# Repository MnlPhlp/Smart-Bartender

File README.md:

# Smart Bartender
This is a modified version of the [smart-bartender](https://youtu.be/2DopvpNF7J4) from Hacker Shack. It can be controlled via a webpage or an alexa skill.

For the building and electronics part watch the video or check the [hackster.io page](https://www.hackster.io/hackershack/smart-bartender-5c430e) of the original project.

## changes in the build
- switched the peristaltic pump for some cheaper and faster water pumps like [these](https://www.ebay.de/itm/131976810073?var=432870985005)
- using a [neopixel ring](https://www.adafruit.com/product/1463) for lighting
- using a [raspberry pi zero](https://www.raspberrypi.org/products/raspberry-pi-zero/) for control

## setup
To setup your pi you need to first install [circuitpython](https://learn.adafruit.com/circuitpython-on-raspberrypi-linux/installing-circuitpython-on-raspberry-pi). After that run:
```
curl https://raw.githubusercontent.com/MnlPhlp/Smart-Bartender/master/setup.sh | bash
```
This will clone the repository, create a venv and install necessary libraries. 
## start
To run the bartender `cd` into Smart-Bartender and start the program with:
```
sudo python bartender.py
```
> sudo is required for the neopixels to work

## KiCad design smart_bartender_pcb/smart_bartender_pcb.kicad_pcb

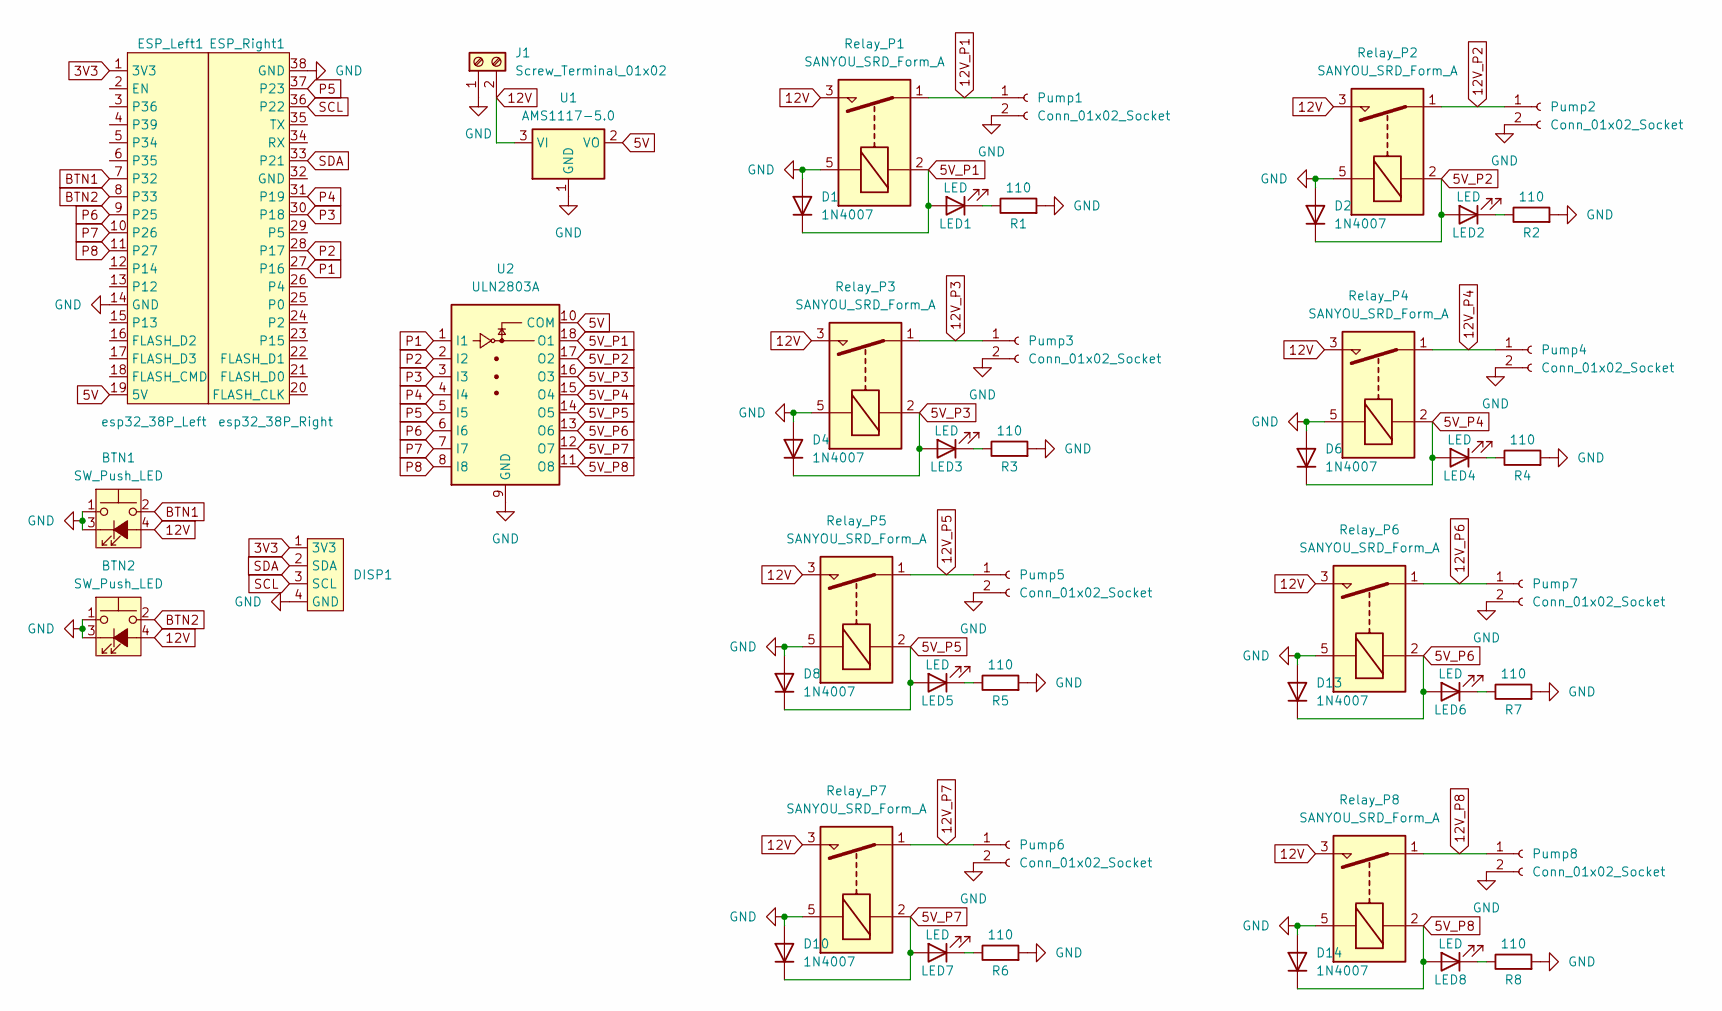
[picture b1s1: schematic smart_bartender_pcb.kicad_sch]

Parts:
BTN1, BTN2: SW_Push_LED; PinHeader_1x04_P2.54mm_Vertical; LCSC C5116483
D1, D2, D4, D6, D8, D10, D13, D14: 1N4007; D_SOD-123; LCSC C3018540
DISP1: PinSocket_1x04_P2.54mm_Horizontal; LCSC C5333413
ESP_Left1: esp32_38P_Left; esp32_38P_left; LCSC C319202
ESP_Right1: esp32_38P_Right; esp32_38P_right; LCSC C319202
J1: Screw_Terminal_01x02; TerminalBlock_Philmore_TB132_1x02_P5.00mm_Horizontal; LCSC C8385
LED1, LED2, LED3, LED4, LED5, LED6, LED7, LED8: LED; LED_0805_2012Metric; LCSC C2297
Pump1, Pump2, Pump3, Pump4, Pump5, Pump6, Pump7, Pump8: Conn_01x02_Socket; SolderWire-1.5sqmm_1x02_P6mm_D1.7mm_OD3mm_Relief
R1, R2, R3, R4, R5, R6, R7, R8: 110; R_0603_1608Metric; LCSC C22781
Relay_P1, Relay_P2, Relay_P3, Relay_P4, Relay_P5, Relay_P6, Relay_P7, Relay_P8: SANYOU_SRD_Form_A; Relay_SPST_SANYOU_SRD_Series_Form_A; LCSC C688862
U1: AMS1117-5.0; SOT-223-3_TabPin2
U2: ULN2803A; SOP-18_7.495x11.515mm_P1.27mm; LCSC C5252904

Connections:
3V3: DISP1.1 (3V3), ESP_Left1.1 (3V3)
5V: ESP_Left1.19 (5V), U1.2 (VO), U2.10 (COM)
5V_P1: D1.1 (K), LED1.2 (A), Relay_P1.2, U2.18 (O1)
5V_P2: D2.1 (K), LED2.2 (A), Relay_P2.2, U2.17 (O2)
5V_P3: D4.1 (K), LED3.2 (A), Relay_P3.2, U2.16 (O3)
5V_P4: D6.1 (K), LED4.2 (A), Relay_P4.2, U2.15 (O4)
5V_P5: D8.1 (K), LED5.2 (A), Relay_P5.2, U2.14 (O5)
5V_P6: D13.1 (K), LED6.2 (A), Relay_P6.2, U2.13 (O6)
5V_P7: D10.1 (K), LED7.2 (A), Relay_P7.2, U2.12 (O7)
5V_P8: D14.1 (K), LED8.2 (A), Relay_P8.2, U2.11 (O8)
12V: BTN1.4 (A), BTN2.4 (A), J1.2, Relay_P1.3, Relay_P2.3, Relay_P3.3, Relay_P4.3, Relay_P5.3, Relay_P6.3, Relay_P7.3, Relay_P8.3, U1.3 (VI)
12V_P1: Pump1.1, Relay_P1.1
12V_P2: Pump2.1, Relay_P2.1
12V_P3: Pump3.1, Relay_P3.1
12V_P4: Pump4.1, Relay_P4.1
12V_P5: Pump5.1, Relay_P5.1
12V_P6: Pump7.1, Relay_P6.1
12V_P7: Pump6.1, Relay_P7.1
12V_P8: Pump8.1, Relay_P8.1
BTN1: BTN1.2, ESP_Left1.7 (P32)
BTN2: BTN2.2, ESP_Left1.8 (P33)
GND: BTN1.1, BTN1.3 (K), BTN2.1, BTN2.3 (K), D1.2 (A), D2.2 (A), D4.2 (A), D6.2 (A), D8.2 (A), D10.2 (A), D13.2 (A), D14.2 (A), DISP1.4 (GND), ESP_Left1.14 (GND), ESP_Right1.38 (GND), J1.1, Pump1.2, Pump2.2, Pump3.2, Pump4.2, Pump5.2, Pump6.2, Pump7.2, Pump8.2, R1.2, R2.2, R3.2, R4.2, R5.2, R6.2, R7.2, R8.2, Relay_P1.5, Relay_P2.5, Relay_P3.5, Relay_P4.5, Relay_P5.5, Relay_P6.5, Relay_P7.5, Relay_P8.5, U1.1 (GND), U2.9 (GND)
unnamed: LED1.1 (K), R1.1
unnamed: LED2.1 (K), R2.1
unnamed: LED3.1 (K), R3.1
unnamed: LED4.1 (K), R4.1
unnamed: LED5.1 (K), R5.1
unnamed: LED6.1 (K), R7.1
unnamed: LED7.1 (K), R6.1
unnamed: LED8.1 (K), R8.1
P1: ESP_Right1.27 (P16), U2.1 (I1)
P2: ESP_Right1.28 (P17), U2.2 (I2)
P3: ESP_Right1.30 (P18), U2.3 (I3)
P4: ESP_Right1.31 (P19), U2.4 (I4)
P5: ESP_Right1.37 (P23), U2.5 (I5)
P6: ESP_Left1.9 (P25), U2.6 (I6)
P7: ESP_Left1.10 (P26), U2.7 (I7)
P8: ESP_Left1.11 (P27), U2.8 (I8)
SCL: DISP1.3 (SCL), ESP_Right1.36 (P22)
SDA: DISP1.2 (SDA), ESP_Right1.33 (P21)

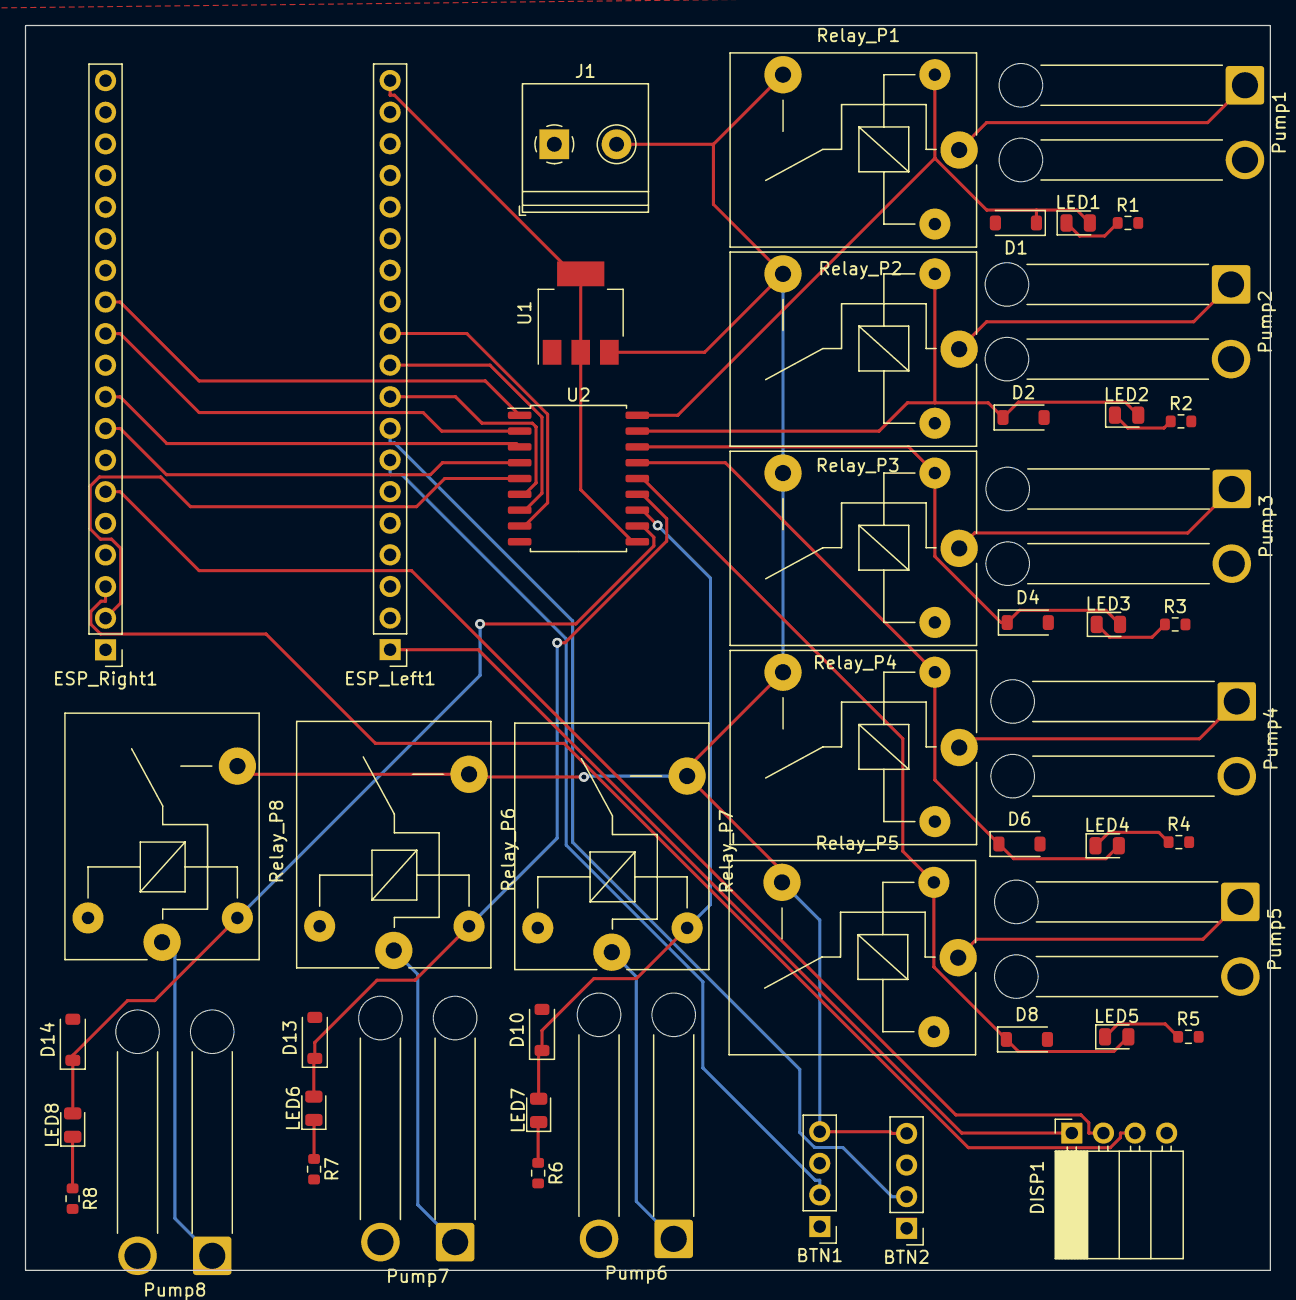
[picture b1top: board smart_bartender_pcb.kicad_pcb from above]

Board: 2 copper layers, 100.0 x 100.0 mm, 48 parts (0 on the bottom side), 40 nets.

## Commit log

2021-05-21 tried to fix for python 3
2021-05-21 changed drawing
2021-05-21 updated requirements
2021-05-21 fixed neopixel pin
2021-05-21 added drinks to test output
2021-05-21 changed font
2021-05-21 created alexa skill
2021-05-23 experiments with grpc
2021-05-23 made api working
2021-05-23 adjusted alexa skill
2021-05-23 added alexa skill to git
2021-05-23 added drink values to skill
2021-05-23 show missing ingredients
2021-05-26 moved files
2021-05-26 switched from GPIO to digitalio library
2021-05-26 implemented stopping with threading event
2021-05-26 added logging
2021-05-26 edited api responses
2021-05-26 set default log level
2021-05-26 renamed api to server
2021-05-26 added index
2021-05-26 added css grid
2021-05-27 fixed button and stop handling
2021-05-27 fixed pump config writing/reading
2021-05-28 added stop button when making drink
2021-05-31 added ssh tunneling
2021-05-31 added stop to alexa skill
2021-05-31 added icon
2021-06-02 added stats
2021-06-02 added date to stats
2021-06-08 added warning on mock display usage
2021-06-08 check alexa userid
2021-06-08 began readme
2021-06-24 fixed setup
2022-04-22 tried getting it to run on pc for testing
2022-06-10 running again :D
2022-06-10 better mocking
2022-06-12 load drinks from api
2022-06-14 basic menu in pc mock
2022-06-30 change logging.warn to logging.warning
2022-06-30 option to reload drinks in config
2024-01-15 started pcb
2024-01-15 started pcb layout
2024-01-15 updated pcb
2024-01-16 move new stuff to separate repo
